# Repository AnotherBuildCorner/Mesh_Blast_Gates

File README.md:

# Mesh_Blast_Gates
## Currently Under Construction

What happens when you combine a Woodworker, and an Electrical Engineer? 
Sometimes the result are things like this. A Mesh controlled set of blast gates for dust collection control.

But first, why did I even bother making this? Cost, and Convenience. Products that can do this already exist on the market. However they cost somewhere around $125 USD PER GATE! Plus additional modules to handle higher power collection 230V systems. Plus I wanted to add advanced features like timers, and a rechargable pocket remote.

On top of that, I already had a fully built system utilizing manually actuated metal blast gates. It really felt like a total waste to rip these gates out in place of some closed solution. And some of the places i wanted to move my existing gates to are inacessible in the course of day to day operation. The commercial option has a switch mounted to the body. Which would impede that solution.

Instead I chose to launch my own system using my pre-existing knowledge of ESP32's and high power hobby servos. 

## Core Architecture.
First things first, the main parts:

The brains of the whole operation. Xiao C6 model ESP 32's. Chosen for their small form factor, while supporing enough GPIO pins to control the system, and supporting a socket mount (A wonderful bit of foresight... More on that later).

Additionally, I wanted a prebuilt serial system for flashing and monitoring, which this provides like many other DEV style boards.

The mechanics driving the actual gates are these servos: 20KG 270 deg servos, Relatively low cost, and when provided enough current/voltage have plenty of torque to do the job.

At right is the actual blast gate for reference.

Interconnect Diagram

A rough picture of the pricing
Per Gate
- $20 per metal gate (already had on hand)
- $10 per servo
- $2 for 100G of 3D print Filament
- $2 misc overhead

Per Control Board as of Febuary 2025
- $5 per XIAO C6
- $1 per PCB
- $1 per Buck Boost Chip
- 1$ per Inductor (I used way oversized ones for low frequency switching)
- $5 rough estimate of additional parts (switches and such)
- $10 per USB power brick and cable (Some of us have mountains of these around) 

Per System cost
- $20 per 24V Transformer
- $10 per 204V-24V contactor
- $2 per 5V signal relay (for the collector control board)
- $5 per Xiao C6 for Collector only
- $20 for a roll of 22 gauge silicon wire for switches

So for my system, which uses 8 gates, 3 control boards, and a relay board the total cost comes up to around...
- Per gate costs: $ 280
- Per Board costs $ 69
- Per System costs $ 57
- Total: $ 416
- for my own cost I already had the blast gates and usb cables on hand, so -$ 190

## Notes:
There are some improvements left to be implemented. The core of which is still better power distribution/control. As well as updating the physical gate structures.
things i'd like to add
### PCB
- Completed desired updates. see V3
### Mechanical

- Add some form of mechanical clutch system.
- - Spring or screw compressed V band on the pinion (spring prefered, but introduces complexity and potential calibrations)
- - Switch from rack and pinion to V wheel and slider with TPU surface
- - add a slider into the rack with a helical spring mounted for bi-directional movement
- - Add TPU teeth to the rack or pinion so they can slip under excessive tension

### Code
- Current code has a strict 1HR timer on dust collection before shutdown
- modify to enable longer run times, or change the switch type specifically for the CNC to enable CNC controlled collection.
- maybe add a custom sender board just for the CNC. Not sure I want hard wires to a tool on wheels... (besides power)
- implement multi-gate control from one switch for cases like multiple gates to one tool
- add a multiple tool mode. Say having the CNC active and a drum sander. 
- consider changing the direct peer-peer mesh to a central node structure. Every time I have to replace one chip, reflashing the entire network is required... and some of the chips are hard to reach. Ideally an auto-detect model would be great.

## V3 

### PCB
V3 PCB is now live. Implementing two desired changes over the V2 Board.
The first is integrating the TVS diodes into the PCB on both the Servo signal lines, as well as the input switches. So far this has prevented any fried servos or bad ESP's in testing.

Second is the Buck-Boost board has been swapped for a commercially available premade PCB. The board provides up to 24V input, and trim controlled output. The PCB also includes a new LED tied directly to the ESP, this LED is programmed to illuminate between 7 and 8V currently to allow calibrating the new board.
The input Bridge Rectifier has been retained, as well as the smoothing cap. This allows for polarity agnotsic DC, as well as AC input for the boards. Currently running on 12V mains.

### Mechanical.
The gear drive system has been slightly refined.
The teeth are now 2mm straight cut gears, with a wider dual guide Rack, and a slot cut into one end to capture the blast gate without additional hardware. The baseplate has been thickened by an additional 2mm. and the gears now feature a multiple cut design on the underside to accomodate multiple servo horn shapes besides the round one. No more skipping of the gears now.

### Code
The system now runs on a central node with a display screen. This way anytime the system is updated (say an ESP dies, or a new board is added) only the new board, and the central node need to be reflashed. Instead of correcting the entire system.
a strict 2 hour timer has been implemented for both short and long press gate openings.

Current sensing is back online in dual ended mode. With a 1.5A current limit, which enforces a chip reset currently. Future updates will force the gate to stop in position. No boards fried yet, but a couple fuses tripped due to user error.

Additionally, the central node has a configurable resend timer. In the past messages were failing to shut down the dust collector as required. With this resend, reliability has reached 100%, although sometimes it can take up to 3 cycles.

Future additions will be to include some kind of current sensing, or non-pushbutton operation perhaps. For things like CNC's with vacuum switching relays, or hall-effect sensors on certain tools. 
Also, the dual gate mode may be updated to set both gates to partially open, to retain system pressure.  TBD.
Lastly, it would be ideal to push all the configuration settings from the central node. so only a preliminary flash will be needed for each endpoint.  For now this is a stretch goal.

### Previous IN PROGRESS notes for V3
Well, as one set of errors is removed, a new set begins to rear its ugly head. 

### PCB
At present a new PCB has not been generated. Currently in the troubleshooting phase.
As it stands right now, it appears the system would function on a metal ducted dust collection system, because the entire tubing would have an ESD potential of 0, being grounded somewhere. However, my system is PVC based, as such it collects static charges.

Initially I did not pursue ESD hardening because I did my best to isolate the switch wires from the dust pipe runs, as well as the servos are on isolated plastic brackets, again with minimum wire near the potentially charged pipes.

However this has not been enough. As it seems the ESP32 chips have been bricking at seemingly random times. Although it always seems to be on a chip that had an active flow of air through a connected gate, which was then switched to a different gate. 

To rectify this, I have placed Unidirectional TVS diodes in two places thus far. The first batch went on each of the input switches connected from signal to ground. This alone did not fix the problem, as shortly after implementing, another board fried.
The second batch is connected from each of the servo signal wires to ground. This setup remains to be tested.

Board with TVS Diodes added: Note, the switches are configured in switch to ground with PULL_UP enabled on the XIAO. So the TVS diodes clamp the voltage to 5V which is within acceptable ranges for the XIAO even though it's a 3.3V microcontroller.

For now I have switched to powering the system on 5V 1A usb power supplies for each module, as I ran out of the Buck controller chips, and as of right now USB power has proven more than powerful enough to control all but my largest gate with the entire system closed and under vacuum. Additionally I encountered some bad wire that had internal insulation problems which shorted out my transformer.  Sometimes it's best to know when to stick with what's working...  I will likely revisit the Buck controller at a later date. First is solving the frying ESP32's  otherwise this system is a useless brick.

## V2
Version 2 corrects a lot of the mistakes Version 1 made, and has resulted in a functional system, but is still far from complete.

### PCBs 
First, the PCB has been updated to contain power limiting safety measures. Among these are Fuse 1, set to a 1 amp glass tube fuse. and the addition of the large curent sense resistor RSense. Additionally a network of voltage dividers has been added to drop the 5-7 volt voltages at Rsense terminals to the 3.3V the ESP ADC can handle.

The system uses dual ended current sensing, with the resistance of Rsense known to within 1% and programmed. Voltage is measured at each terminal, the difference calculated, and from that current through the resistor is determined. This is used to initiate a restart in the code. As the gates are programmed to not move until a command is sent, this functions as a pause. This is temporary, in time a better response to a binding gate, like bounce or a simple stop will be implemented.

Additionally, a second PCB for controlling two possible Dust collection units has been added.

### Mechanical

On the mechanical aspect, the piston arrangement has been replaced with a rack and pinion. 
Advantages
- More positive mechanical engagement
- less servo torque required for actuation
- uses more of the available 270deg servo throw

Disadvantages
- takes up more space due to the rack
- also requires more material to 3D print increasing overall cost
- the gears can sometimes skip (this is more a poor implementation than a flaw of the rack itself)
- without precise limits in the code, binding, or semi-open gates are a problem. Yet somehow for identical parts, the limits are sightly different for each gate.

More precisely, a Herringbone rack and pinion was 3D printed.The herringbone is specifically for it's self aligning aspect, so the rack is unlikely to slip off the pinion without being captured somehow.

[Rack and Pinion in operation.mov](<Photos/V2/Gate Operation.MOV>)

## V1
It's safe to consider this a very flawed early prototype. A lot of mistakes were made.
Primarily you will note the absence of any sort of fuses/safety devices. This will really come back to bite later.

The problem is the system is a semi-closed loop design. I say that because internally each servo is closed loop, It knows its position, and the desired target position. However this position does not make it back to the contol board. So to the controller, the system is open loop.

Why is this a problem? Because each control board is fed a set of target limits for open and close. And the servo will either reach that position, or push until it's internal overload trips. Problem is the servo can pull upwards of 5A at 7V in "stall" operation. which is way more than the Buck controller is rated for.

Now under normal circumstances this isn't an issue, as the programming has delays designed to slow the servo's operation, lowering the current output. However, on startup sometimes the gates are in the wrong place, as power off location memory has not been implemented yet, and attempt to return home rapidly. Or the limits get slightly out of whack, and the servo stalls. When supplied by USB power, this isn't an issue, as the XIAO's internal brownout detector triggers. But with this external supply that limiter doesn't exist. So instead, fried Buck chips, and not the edible kind either.

### Mechanical

The problems above were exacerbated by a poor choice of mechanical arrangement. The first iteration used a piston like arrangement. Which in practice was great on opening. But tended to bind horribly on close, stalling the servo, and yes, you guessed it, fried chips.

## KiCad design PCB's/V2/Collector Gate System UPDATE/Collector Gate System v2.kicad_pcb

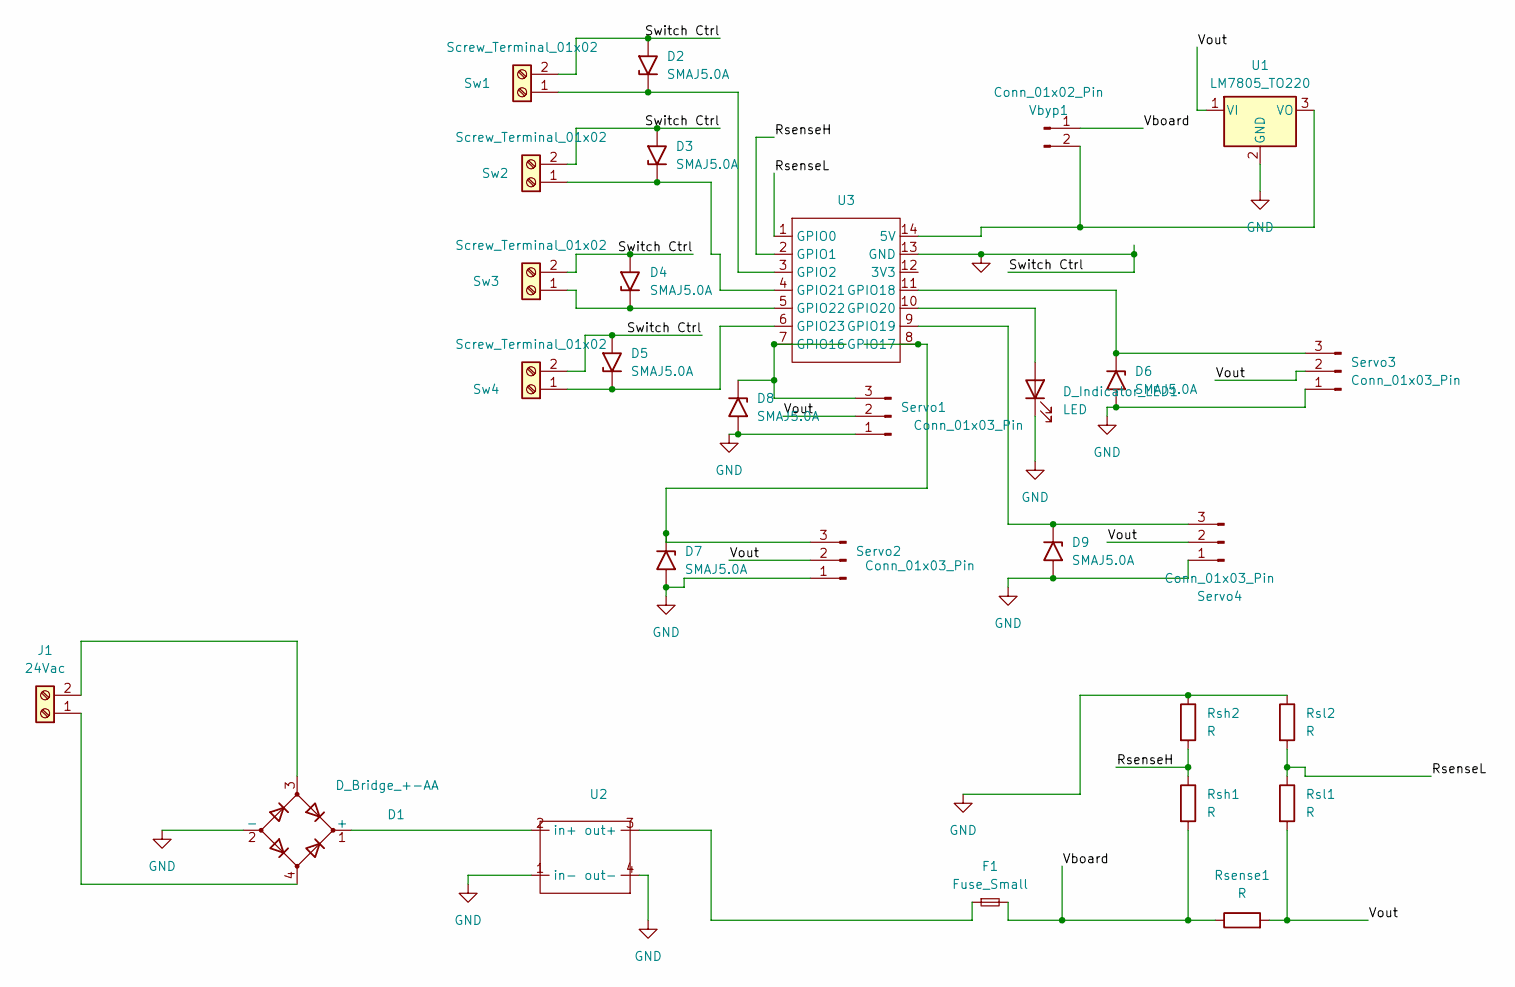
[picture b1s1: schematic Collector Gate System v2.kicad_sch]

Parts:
D1: D_Bridge_+-AA; DB_M
D2, D3, D4, D5, D6, D7, D8, D9: SMAJ5.0A; D_SMA
D_Indicator_LED1: LED; LED_D5.0mm_Clear
F1: Fuse_Small; Fuseholder_Clip-5x20mm_Keystone_3512P_Inline_P23.62x7.27mm_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
J1: 24Vac; TerminalBlock_Altech_AK300-2_P5.00mm
Rsense1: R; R_Axial_DIN0414_L11.9mm_D4.5mm_P15.24mm_Horizontal
Rsh1, Rsh2: R; R_0603_1608Metric_Pad0.98x0.95mm_HandSolder
Rsl1, Rsl2: R; R_0603_1608Metric_Pad0.98x0.95mm_HandSolder
Servo1, Servo2, Servo3, Servo4: Conn_01x03_Pin; PinHeader_1x03_P2.54mm_Vertical
Sw1, Sw2, Sw3, Sw4: Screw_Terminal_01x02; CONN_1985195
U1: LM7805_TO220; TO-220-3_Vertical
U2: MS1584_fullboard
U3: XIAO-Generic-Thruhole-14P-2.54-21X17.8MM
Vbyp1: Conn_01x02_Pin; PinHeader_1x02_P2.54mm_Vertical

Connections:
/RsenseH: Rsh1.1, Rsh2.2, U3.2 (GPIO1)
/RsenseL: Rsl1.1, Rsl2.2, U3.1 (GPIO0)
/Vboard: F1.2, Rsense1.1, Rsh1.2, Vbyp1.1
/Vout: Rsense1.2, Rsl1.2, Servo1.2, Servo2.2, Servo3.2, Servo4.2, U1.1 (VI)
GND: D1.2 (-), D2.2 (A2), D3.2 (A2), D4.2 (A2), D5.2 (A2), D6.2 (A2), D7.2 (A2), D8.2 (A2), D9.2 (A2), D_Indicator_LED1.1 (K), Rsh2.1, Rsl2.1, Servo1.1, Servo2.1, Servo3.1, Servo4.1, Sw1.2, Sw2.2, Sw3.2, Sw4.2, U1.2 (GND), U2.1 (in-), U2.4 (out-), U3.13 (GND)
unnamed: D1.1 (+), U2.2 (in+)
unnamed: D2.1 (A1), Sw1.1, U3.3 (GPIO2)
unnamed: D3.1 (A1), Sw2.1, U3.4 (GPIO21)
unnamed: D4.1 (A1), Sw3.1, U3.5 (GPIO22)
unnamed: D5.1 (A1), Sw4.1, U3.6 (GPIO23)
unnamed: D6.1 (A1), Servo3.3, U3.11 (GPIO18)
unnamed: D7.1 (A1), Servo2.3, U3.8 (GPIO17)
unnamed: D8.1 (A1), Servo1.3, U3.7 (GPIO16)
unnamed: D9.1 (A1), Servo4.3, U3.9 (GPIO19)
unnamed: D_Indicator_LED1.2 (A), U3.10 (GPIO20)
unnamed: D1.4, J1.1
unnamed: D1.3, J1.2
unnamed: U1.3 (VO), U3.14 (5V), Vbyp1.2
unnamed: F1.1, U2.3 (out+)

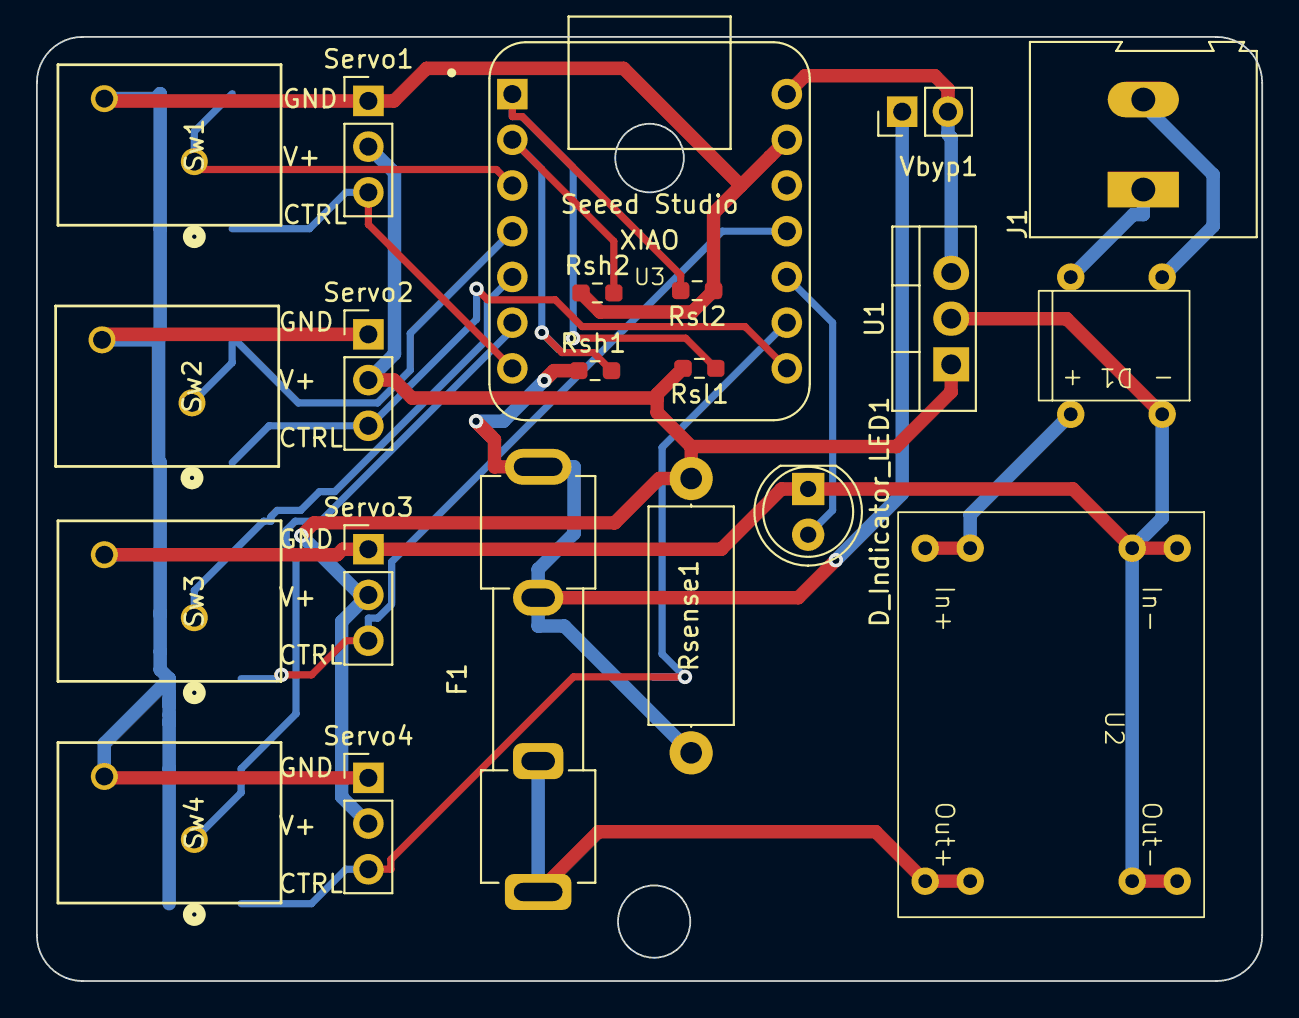
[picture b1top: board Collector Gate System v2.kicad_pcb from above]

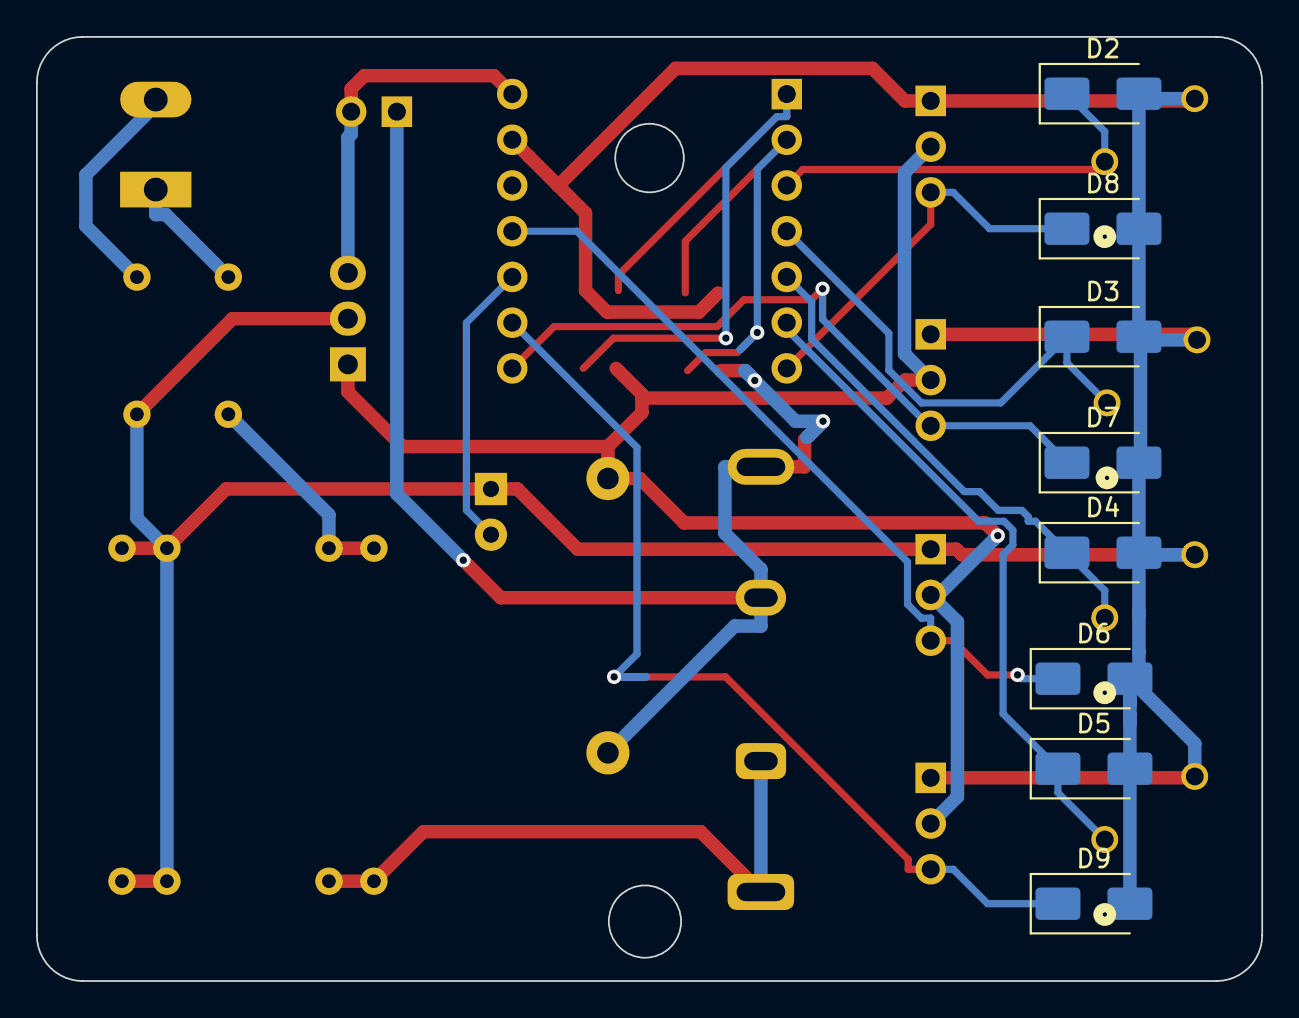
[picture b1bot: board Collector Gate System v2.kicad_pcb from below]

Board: 2 copper layers, 68.1 x 52.5 mm, 29 parts (8 on the bottom side), 19 nets.

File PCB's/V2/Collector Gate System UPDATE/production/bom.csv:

Designator,Footprint,Quantity,Value,LCSC Part #
D1,DB_M,1,D_Bridge_+-AA,
"D2, D3, D4, D5, D6, D7, D8, D9",D_SMA,8,SMAJ5.0A,
D_INDICATOR_LED1,LED_D5.0mm_Clear,1,LED,
F1,Fuseholder_Clip-5x20mm_Keystone_3512P_Inline_P23.62x7.27mm_D1.02x2.41x1.02x1.57mm_Horizontal,1,Fuse_Small,
J1,TerminalBlock_Altech_AK300-2_P5.00mm,1,24Vac,
RSENSE1,R_Axial_DIN0414_L11.9mm_D4.5mm_P15.24mm_Horizontal,1,R,
"RSH1, RSH2, RSL1, RSL2",0603,4,R,
"SERVO1, SERVO2, SERVO3, SERVO4",PinHeader_1x03_P2.54mm_Vertical,4,Conn_01x03_Pin,
"SW1, SW2, SW3, SW4",CONN_1985195,4,Screw_Terminal_01x02,
U1,TO-220-3_Vertical,1,LM7805_TO220,
U2,MS1584_fullboard,1,~,
U3,XIAO-Generic-Thruhole-14P-2.54-21X17.8MM,1,~,
VBYP1,PinHeader_1x02_P2.54mm_Vertical,1,Conn_01x02_Pin,

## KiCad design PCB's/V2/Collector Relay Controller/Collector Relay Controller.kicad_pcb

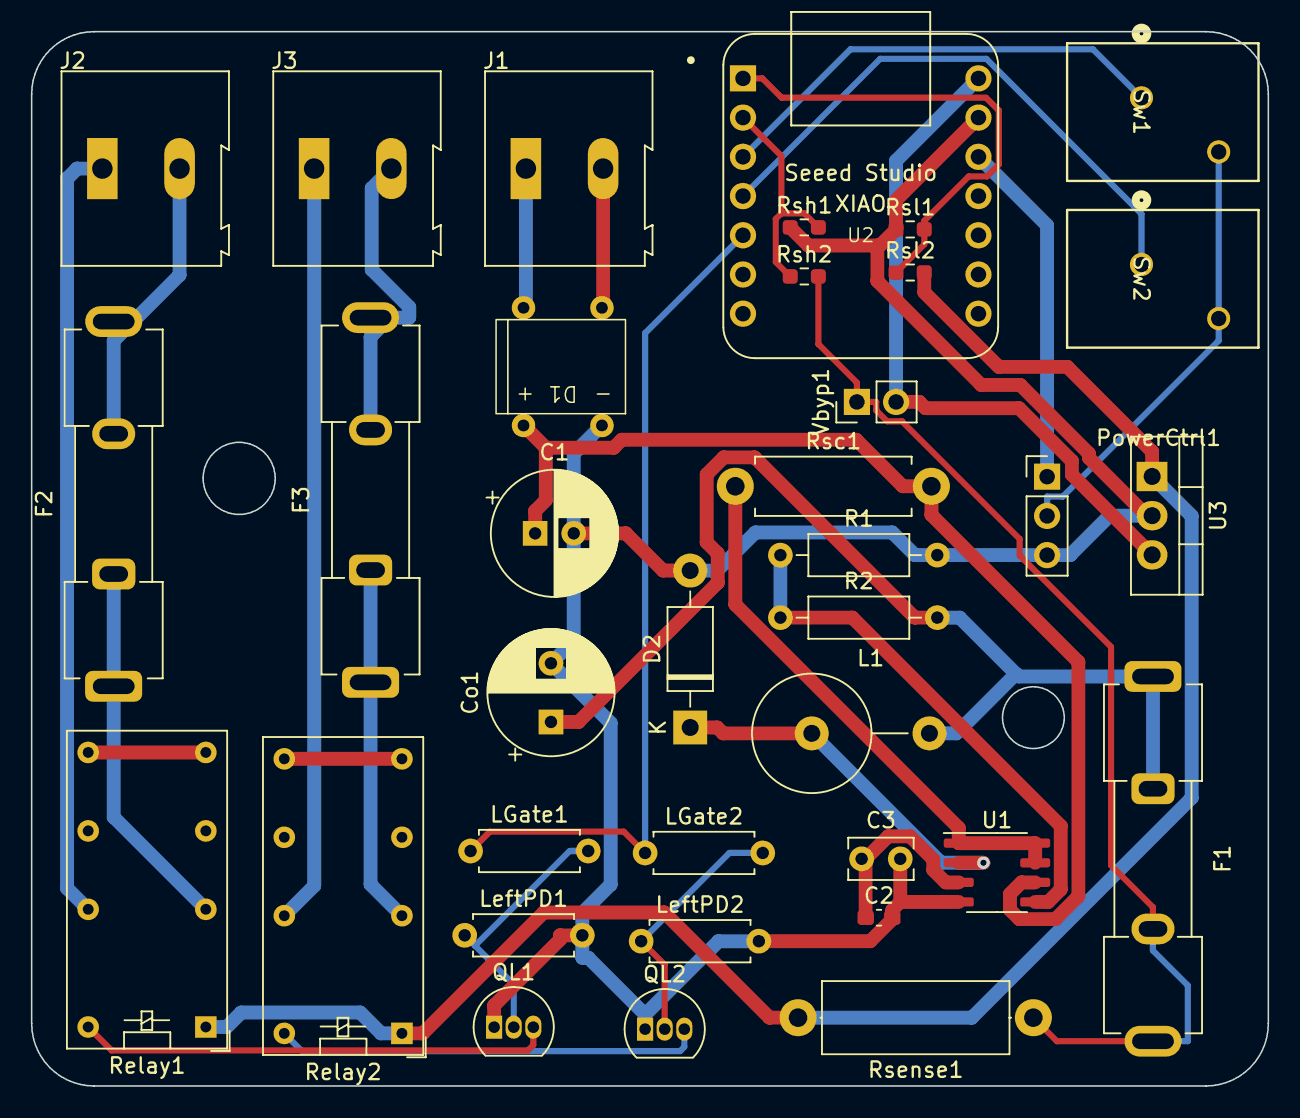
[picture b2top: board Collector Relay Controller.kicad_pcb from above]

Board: 2 copper layers, 80.1 x 68.3 mm, 36 parts (0 on the bottom side), 31 nets.

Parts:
C1: C_Polarized; CP_Radial_D8.0mm_P2.50mm
C2: Ct; C_0603_1608Metric_Pad1.08x0.95mm_HandSolder
C3: Ct; C_Rect_L4.0mm_W2.5mm_P2.50mm
Co1: C_Polarized; CP_Radial_D8.0mm_P3.80mm
D1: D_Bridge_+-AA; DB_M
D2: 1N5819; D_DO-41_SOD81_P10.16mm_Horizontal
F1, F2, F3: Fuse_Small; Fuseholder_Clip-5x20mm_Keystone_3512P_Inline_P23.62x7.27mm_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
J1: 24Vac; TerminalBlock_Altech_AK300-2_P5.00mm
J2, J3: Contactor1; TerminalBlock_Altech_AK300-2_P5.00mm
L1: L; L_Axial_L16.0mm_D7.5mm_P7.62mm_Vertical_Fastron_XHBCC
LGate1, LGate2: R; R_Axial_DIN0207_L6.3mm_D2.5mm_P7.62mm_Horizontal
LeftPD1, LeftPD2: R; R_Axial_DIN0207_L6.3mm_D2.5mm_P7.62mm_Horizontal
PowerCtrl1: Conn_01x03_Pin; PinHeader_1x03_P2.54mm_Vertical
QL1, QL2: 2N7000; TO-92_Inline
R1, R2: R; R_Axial_DIN0207_L6.3mm_D2.5mm_P10.16mm_Horizontal
Relay1, Relay2: G5V-2; Relay_DPDT_Omron_G5V-2
Rsc1: R; R_Axial_DIN0411_L9.9mm_D3.6mm_P12.70mm_Horizontal
Rsense1: R; R_Axial_DIN0414_L11.9mm_D4.5mm_P15.24mm_Horizontal
Rsh1, Rsh2: R; R_0603_1608Metric_Pad0.98x0.95mm_HandSolder
Rsl1, Rsl2: R; R_0603_1608Metric_Pad0.98x0.95mm_HandSolder
Sw1, Sw2: Screw_Terminal_01x02; CONN_1985195
U1: MC33063AD; SOIC-8_3.9x4.9mm_P1.27mm
U2: XIAO-Generic-Thruhole-14P-2.54-21X17.8MM
U3: LM7805_TO220; TO-220-3_Vertical
Vbyp1: Conn_01x02_Pin; PinHeader_1x02_P2.54mm_Vertical

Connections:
/Control1: LGate1.1, LGate2.1, U2.5 (GPIO22)
/RsenseH: Rsh1.2, Rsh2.1, U2.2 (GPIO1)
/RsenseL: Rsl1.2, Rsl2.1, U2.1 (GPIO0)
/Switch Ctrl: PowerCtrl1.2, Sw1.2, Sw2.2
/Vboard: F1.2, Rsense1.1, Rsh2.2, Vbyp1.1
/Vout: Relay1.1, Relay2.1, Rsense1.2, Rsl2.2, U3.1 (VI)
GND: C1.2, C2.2, C3.2, Co1.2, D1.2 (-), D2.2 (A), LeftPD1.2, LeftPD2.2, PowerCtrl1.3, QL1.1 (S), QL2.1 (S), R1.2, Rsh1.1, Rsl1.1, U1.4 (GND), U2.13 (GND), U3.2 (GND)
unnamed: Co1.1, F1.1, L1.2, R2.2
unnamed: C1.1, D1.1 (+), Rsc1.2, U1.6 (Vin)
unnamed: D2.1 (K), L1.1, U1.2 (SwE)
unnamed: F2.1, Relay1.4
unnamed: F3.1, Relay2.4
unnamed: D1.4, J1.1
unnamed: D1.3, J1.2
unnamed: J2.1, Relay1.13
unnamed: F2.2, J2.2
unnamed: J3.1, Relay2.13
unnamed: F3.2, J3.2
unnamed: PowerCtrl1.1, U2.12 (3V3)
unnamed: QL1.3 (D), Relay1.16
unnamed: LGate1.2, LeftPD1.1, QL1.2 (G)
unnamed: QL2.3 (D), Relay2.16
unnamed: LGate2.2, LeftPD2.1, QL2.2 (G)
unnamed: Relay1.8, Relay1.9
unnamed: Relay2.8, Relay2.9
unnamed: Sw1.1, U2.3 (GPIO2)
unnamed: Sw2.1, U2.4 (GPIO21)
unnamed: Rsc1.1, U1.1 (SwC), U1.7 (Ipk), U1.8 (DC)
unnamed: C2.1, C3.1, U1.3 (TC)
unnamed: R1.1, R2.1, U1.5 (Vfb)
unnamed: U2.14 (5V), U3.3 (VO), Vbyp1.2

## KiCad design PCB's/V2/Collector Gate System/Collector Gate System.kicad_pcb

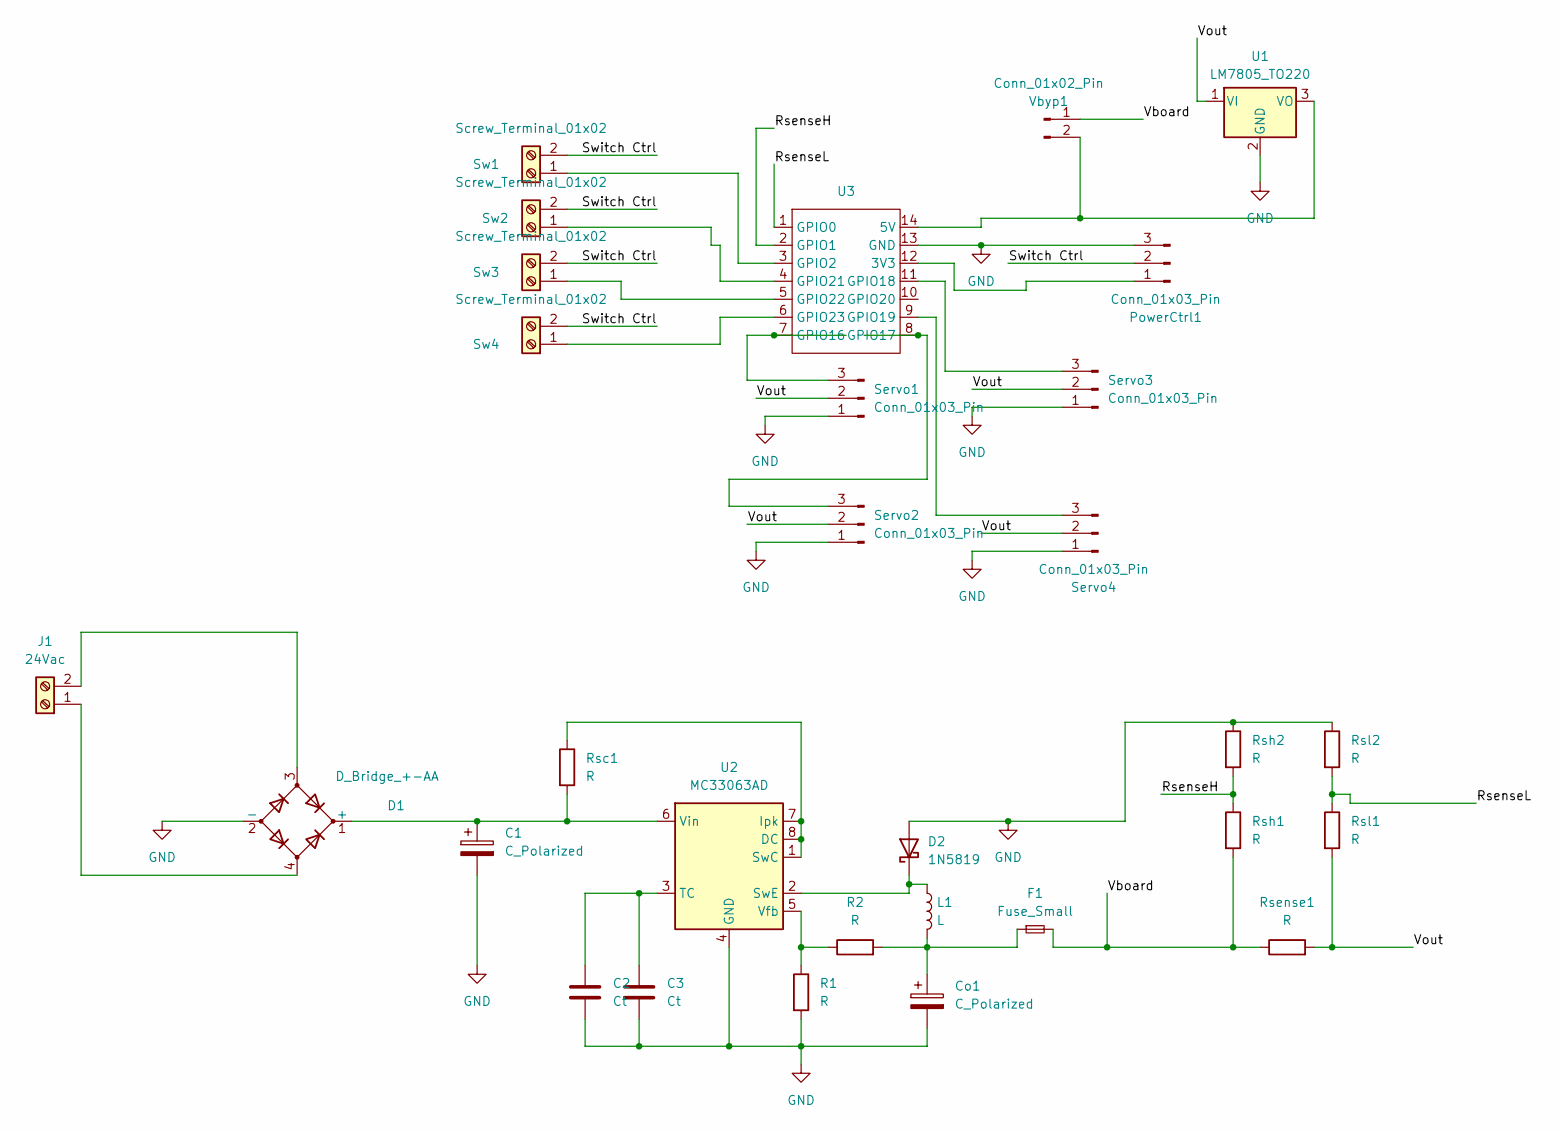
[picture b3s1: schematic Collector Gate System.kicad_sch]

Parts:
C1: C_Polarized; CP_Radial_D8.0mm_P2.50mm
C2: Ct; C_0603_1608Metric_Pad1.08x0.95mm_HandSolder
C3: Ct; C_Rect_L4.0mm_W2.5mm_P2.50mm
Co1: C_Polarized; CP_Radial_D8.0mm_P3.80mm
D1: D_Bridge_+-AA; DB_M
D2: 1N5819; D_DO-41_SOD81_P10.16mm_Horizontal
F1: Fuse_Small; Fuseholder_Clip-5x20mm_Keystone_3512P_Inline_P23.62x7.27mm_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
J1: 24Vac; TerminalBlock_Altech_AK300-2_P5.00mm
L1: L; L_Axial_L16.0mm_D7.5mm_P7.62mm_Vertical_Fastron_XHBCC
PowerCtrl1: Conn_01x03_Pin; PinHeader_1x03_P2.54mm_Vertical
R1, R2: R; R_Axial_DIN0207_L6.3mm_D2.5mm_P10.16mm_Horizontal
Rsc1: R; R_Axial_DIN0411_L9.9mm_D3.6mm_P12.70mm_Horizontal
Rsense1: R; R_Axial_DIN0414_L11.9mm_D4.5mm_P15.24mm_Horizontal
Rsh1, Rsh2: R; R_0603_1608Metric_Pad0.98x0.95mm_HandSolder
Rsl1, Rsl2: R; R_0603_1608Metric_Pad0.98x0.95mm_HandSolder
Servo1, Servo2, Servo3, Servo4: Conn_01x03_Pin; PinHeader_1x03_P2.54mm_Vertical
Sw1, Sw2, Sw3, Sw4: Screw_Terminal_01x02; CONN_1985195
U1: LM7805_TO220; TO-220-3_Vertical
U2: MC33063AD; SOIC-8_3.9x4.9mm_P1.27mm
U3: XIAO-Generic-Thruhole-14P-2.54-21X17.8MM
Vbyp1: Conn_01x02_Pin; PinHeader_1x02_P2.54mm_Vertical

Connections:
/RsenseH: Rsh1.1, Rsh2.2, U3.2 (GPIO1)
/RsenseL: Rsl1.1, Rsl2.2, U3.1 (GPIO0)
/Switch Ctrl: PowerCtrl1.2, Sw1.2, Sw2.2, Sw3.2, Sw4.2
/Vboard: F1.2, Rsense1.1, Rsh1.2, Vbyp1.1
/Vout: Rsense1.2, Rsl1.2, Servo1.2, Servo2.2, Servo3.2, Servo4.2, U1.1 (VI)
GND: C1.2, C2.2, C3.2, Co1.2, D1.2 (-), D2.2 (A), PowerCtrl1.3, R1.2, Rsh2.1, Rsl2.1, Servo1.1, Servo2.1, Servo3.1, Servo4.1, U1.2 (GND), U2.4 (GND), U3.13 (GND)
unnamed: Co1.1, F1.1, L1.2, R2.2
unnamed: C1.1, D1.1 (+), Rsc1.2, U2.6 (Vin)
unnamed: D2.1 (K), L1.1, U2.2 (SwE)
unnamed: D1.4, J1.1
unnamed: D1.3, J1.2
unnamed: PowerCtrl1.1, U3.12 (3V3)
unnamed: Servo1.3, U3.7 (GPIO16)
unnamed: Servo2.3, U3.8 (GPIO17)
unnamed: Servo3.3, U3.11 (GPIO18)
unnamed: Servo4.3, U3.9 (GPIO19)
unnamed: Sw1.1, U3.3 (GPIO2)
unnamed: Sw2.1, U3.4 (GPIO21)
unnamed: Sw3.1, U3.5 (GPIO22)
unnamed: Sw4.1, U3.6 (GPIO23)
unnamed: U1.3 (VO), U3.14 (5V), Vbyp1.2
unnamed: Rsc1.1, U2.1 (SwC), U2.7 (Ipk), U2.8 (DC)
unnamed: C2.1, C3.1, U2.3 (TC)
unnamed: R1.1, R2.1, U2.5 (Vfb)

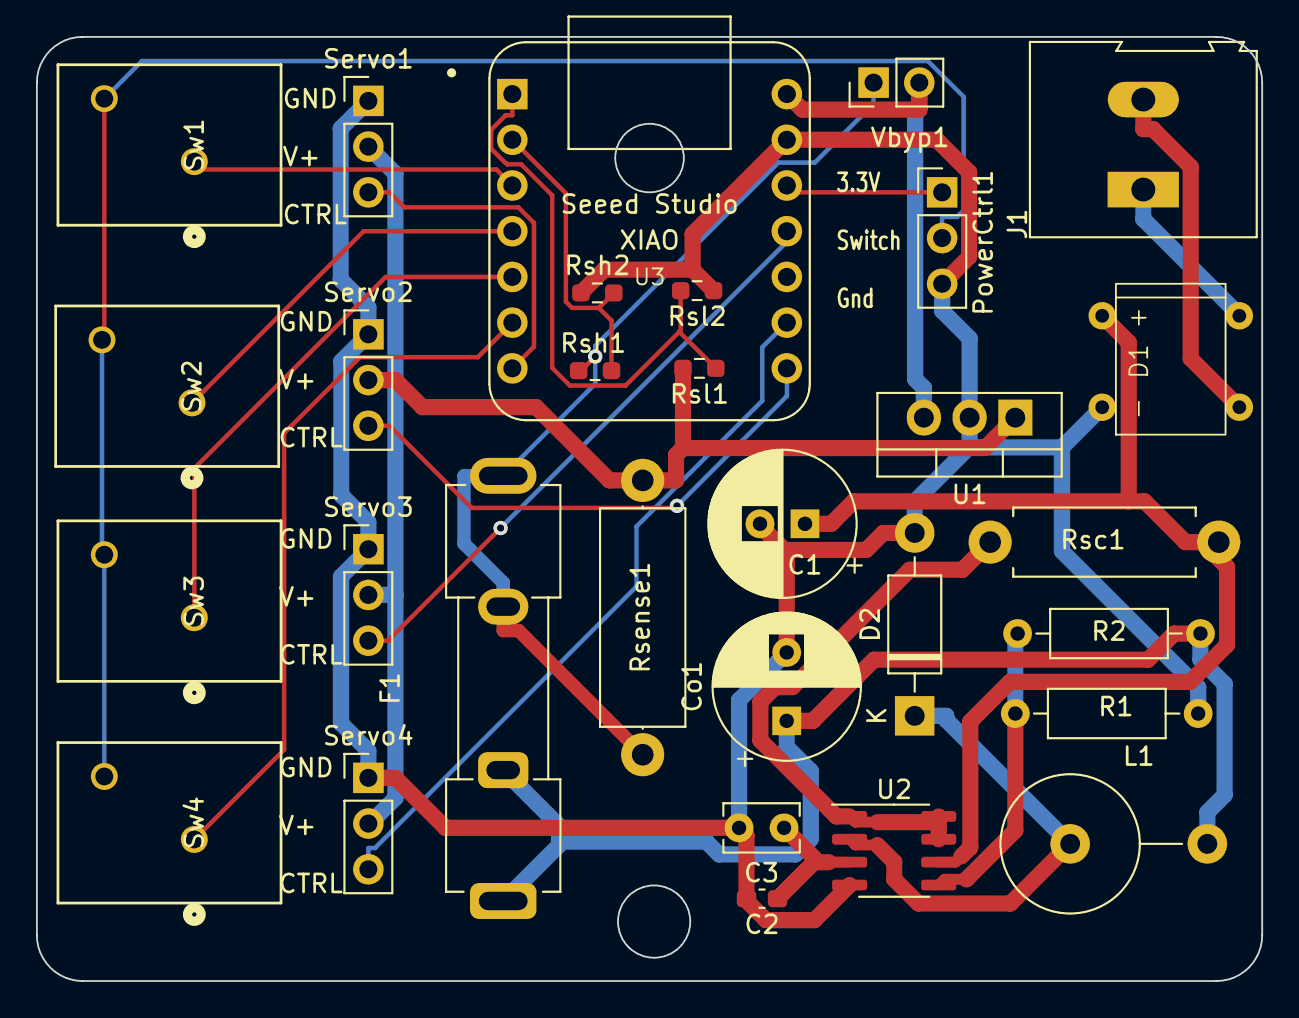
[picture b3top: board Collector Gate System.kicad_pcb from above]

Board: 2 copper layers, 68.1 x 52.5 mm, 30 parts (0 on the bottom side), 24 nets.

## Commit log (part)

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2025-02-10 Added Untitled Diagram.drawio
2025-02-10 new photos
2025-02-10 Code Files and Readme
2025-02-10 move
2025-02-10 updated link
2025-02-10 added TVS
2025-02-14 new code versions
2025-02-14 Mesh Working , preparing TESTLED
2025-02-15 Ready except current sensing controls
2025-02-15 Looks to be complete e xcept power monitoring
2025-02-15 updated for clarity, wifi acting up
2025-02-15 Anakin: ITS WORKING!!!
2025-02-15 Working
2025-02-15 LEDs dont play with Wifi, Timers enabled
2025-02-28 added screen to control node
2025-05-09 last commit
2025-05-14 added constant central check/resent to cover fringe cases
2025-08-09 load
2025-08-09 re-enabled current sensing added LED
2025-08-13 re-enabled current sense, added Vref LED
2025-09-14 V3 Live
2025-10-02 link
